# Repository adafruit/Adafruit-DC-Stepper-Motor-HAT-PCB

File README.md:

## Adafruit DC Stepper Motor HAT and Bonnet PCB
<a href="http://www.adafruit.com/products/2348"><br/>
Click here to purchase one from the Adafruit shop</a>

Let your robotic dreams come true with the new DC+Stepper Motor HAT from Adafruit. This Raspberry Pi add-on is perfect for any motion project as it can drive up to 4 DC or 2 Stepper motors with full PWM speed control.

Raspberry Pi and motors are not included. Works with any and all Raspberry Pi computers with 2x20 connection port.

Since the Raspberry Pi does not have a lot of PWM pins, we use a fully-dedicated PWM driver chip onboard to both control motor direction and speed. This chip handles all the motor and speed controls over I2C. Only two pins (SDA & SCL) are required to drive the multiple motors, and since it's I2C you can also connect any other I2C devices or HATs to the same pins.

In fact, you can even stack multiple Motor HATs, up to 32 of them, for controlling up to 64 stepper motors or 128 DC motors (or a mix of the two) - just remember to purchase and solder in a stacking header instead of the one we include.

Motors are controlled by TB6612 MOSFET drivers with 1.2A per channel current capability (you can draw up to 3A peak for approx 20ms at a time), a big improvement over L293D drivers and there are built-in flyback diodes as well.

PCB files for the Adafruit DC Stepper Motor Hat and Bonnet. The format is EagleCAD schematic and board layout
- https://www.adafruit.com/products/2348
- https://www.adafruit.com/product/4280

### License

Adafruit invests time and resources providing this open source design, please support Adafruit and open-source hardware by purchasing products from [Adafruit](https://www.adafruit.com)!

All text above must be included in any redistribution

Designed by Limor Fried/Ladyada for Adafruit Industries.
Creative Commons Attribution/Share-Alike, all text above must be included in any redistribution. 
See license.txt for additional information.

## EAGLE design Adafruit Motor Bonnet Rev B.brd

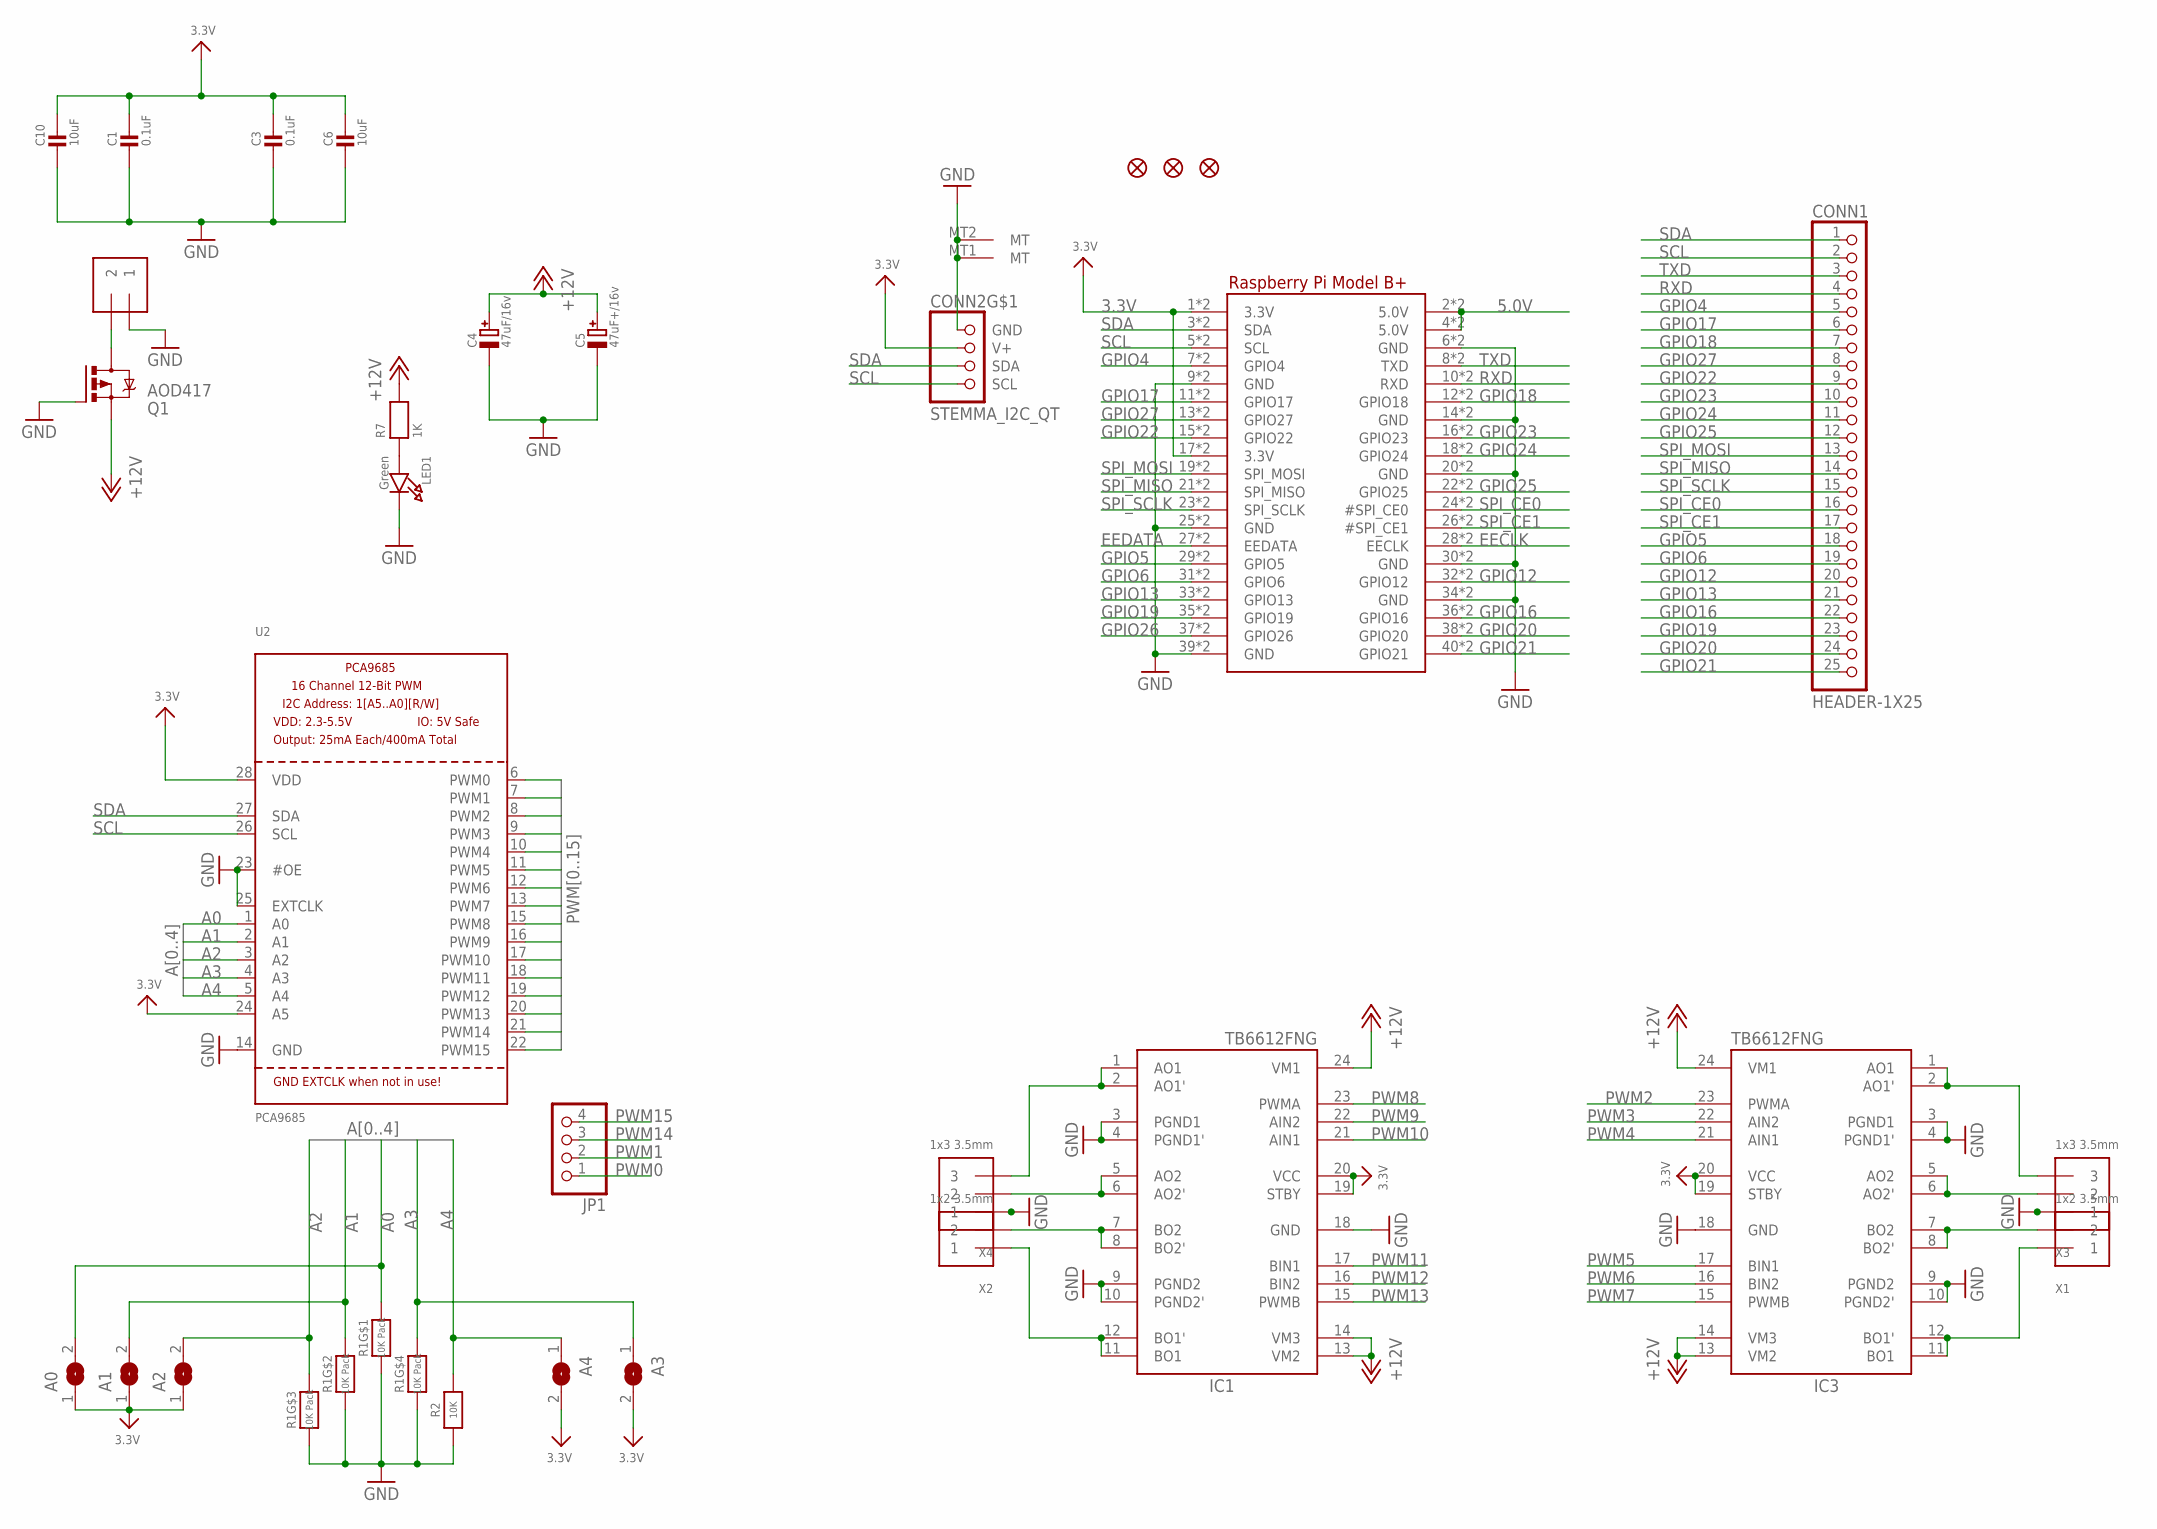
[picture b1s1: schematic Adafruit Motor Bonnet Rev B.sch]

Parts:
A0, A1, A2, A3, A4: SOLDERJUMPERREFLOW_NOPASTE; SOLDERJUMPER_REFLOW_NOPASTE
C1, C3: 0.1uF; 0603-NO
C4: 47uF/16v; PANASONIC_C
C5: 47uF+/16v; PANASONIC_C
C6, C10: 10uF; 0805-NO
CONN1: HEADER-1X25; 1X25_ROUND_70MIL
CONN2: STEMMA_I2C_QT; JST_SH4
FID1, FID2, FID3: FIDUCIAL_1MM
IC1, IC3: TB6612FNG; SSOP24
JP1: HEADER-1X4ROUND; 1X04_ROUND
LED1: Green; CHIPLED_0805_NOOUTLINE
MPOWER: 1x2 3.5mm; TERMBLOCK_1X2-3.5MM
Q1: AOD417; D-PAK_TO252AA
R1: 10K Pack; RESPACK_4X0603
R2: 10K; 0603-NO
R7: 1K; 0603-NO
RPI1: RASPBERRYPI_BPLUS_BONNET_THMSMT; PI_BONNET_THMSMT
U2: PCA9685; TSSOP28
X1, X2: 1x2 3.5mm; TERMBLOCK_1X2-3.5MM
X3, X4: 1x3 3.5mm; TERMBLOCK_1X3-3.5MM

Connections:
3.3V: A0.1, A1.1, A2.1, A3.2, A4.2, C1.1, C3.1, C6.1, C10.1, CONN2.2 (V+), IC1.19 (STBY), IC1.20 (VCC), IC3.19 (STBY), IC3.20 (VCC), RPI1.1 (3.3V), RPI1.17 (3.3V), RPI1.S1 (3.3V), RPI1.S17 (3.3V), U2.24 (A5), U2.28 (VDD)
5.0V: RPI1.2 (5.0V), RPI1.4 (5.0V), RPI1.S2 (5.0V), RPI1.S4 (5.0V)
+12V: C4.+, C5.+, IC1.13 (VM2), IC1.14 (VM3), IC1.24 (VM1), IC3.13 (VM2), IC3.14 (VM3), IC3.24 (VM1), Q1.3 (S), R7.2
A0: A0.2, R1.8 (2), U2.1 (A0)
A1: A1.2, R1.7 (2), U2.2 (A1)
A2: A2.2, R1.6 (2), U2.3 (A2)
A3: A3.1, R1.5 (2), U2.4 (A3)
A4: A4.1, R2.2, U2.5 (A4)
EECLK: RPI1.28 (EECLK), RPI1.S28 (EECLK)
EEDATA: RPI1.27 (EEDATA), RPI1.S27 (EEDATA)
GND: C1.2, C3.2, C4.-, C5.-, C6.2, C10.2, CONN2.1 (GND), CONN2.MT1 (MT), CONN2.MT2 (MT), IC1.3 (PGND1), IC1.4 (PGND1'), IC1.9 (PGND2), IC1.10 (PGND2'), IC1.18 (GND), IC3.3 (PGND1), IC3.4 (PGND1'), IC3.9 (PGND2), IC3.10 (PGND2'), IC3.18 (GND), LED1.C, MPOWER.1, Q1.1 (G), R1.1, R1.2 (1), R1.3 (1), R1.4 (1), R2.1, RPI1.6 (GND), RPI1.9 (GND), RPI1.14 (GND), RPI1.20 (GND), RPI1.25 (GND), RPI1.30 (GND), RPI1.34 (GND), RPI1.39 (GND), RPI1.S6 (GND), RPI1.S9 (GND), RPI1.S14 (GND), RPI1.S20 (GND), RPI1.S25 (GND), RPI1.S30 (GND), RPI1.S34 (GND), RPI1.S39 (GND), U2.14 (GND), U2.23 (#OE), U2.25 (EXTCLK), X3.1, X4.1
GPIO4: CONN1.5, RPI1.7 (GPIO4), RPI1.S7 (GPIO4)
GPIO5: CONN1.18, RPI1.29 (GPIO5), RPI1.S29 (GPIO5)
GPIO6: CONN1.19, RPI1.31 (GPIO6), RPI1.S31 (GPIO6)
GPIO12: CONN1.20, RPI1.32 (GPIO12), RPI1.S32 (GPIO12)
GPIO13: CONN1.21, RPI1.33 (GPIO13), RPI1.S33 (GPIO13)
GPIO16: CONN1.22, RPI1.36 (GPIO16), RPI1.S36 (GPIO16)
GPIO17: CONN1.6, RPI1.11 (GPIO17), RPI1.S11 (GPIO17)
GPIO18: CONN1.7, RPI1.12 (GPIO18), RPI1.S12 (GPIO18)
GPIO19: CONN1.23, RPI1.35 (GPIO19), RPI1.S35 (GPIO19)
GPIO20: CONN1.24, RPI1.38 (GPIO20), RPI1.S38 (GPIO20)
GPIO21: CONN1.25, RPI1.40 (GPIO21), RPI1.S40 (GPIO21)
GPIO22: CONN1.9, RPI1.15 (GPIO22), RPI1.S15 (GPIO22)
GPIO23: CONN1.10, RPI1.16 (GPIO23), RPI1.S16 (GPIO23)
GPIO24: CONN1.11, RPI1.18 (GPIO24), RPI1.S18 (GPIO24)
GPIO25: CONN1.12, RPI1.22 (GPIO25), RPI1.S22 (GPIO25)
GPIO26: RPI1.37 (GPIO26), RPI1.S37 (GPIO26)
GPIO27: CONN1.8, RPI1.13 (GPIO27), RPI1.S13 (GPIO27)
M1A: IC1.1 (AO1), IC1.2 (AO1'), X4.3
M1B: IC1.5 (AO2), IC1.6 (AO2'), X4.2
M2A: IC1.11 (BO1), IC1.12 (BO1'), X2.1
M2B: IC1.7 (BO2), IC1.8 (BO2'), X2.2
M3A: IC3.1 (AO1), IC3.2 (AO1'), X3.3
M3B: IC3.5 (AO2), IC3.6 (AO2'), X3.2
M4A: IC3.11 (BO1), IC3.12 (BO1'), X1.1
M4B: IC3.7 (BO2), IC3.8 (BO2'), X1.2
unnamed: LED1.A, R7.1
PWM0: JP1.1, U2.6 (PWM0)
PWM1: JP1.2, U2.7 (PWM1)
PWM2: IC3.23 (PWMA), U2.8 (PWM2)
PWM3: IC3.22 (AIN2), U2.9 (PWM3)
PWM4: IC3.21 (AIN1), U2.10 (PWM4)
PWM5: IC3.17 (BIN1), U2.11 (PWM5)
PWM6: IC3.16 (BIN2), U2.12 (PWM6)
PWM7: IC3.15 (PWMB), U2.13 (PWM7)
PWM8: IC1.23 (PWMA), U2.15 (PWM8)
PWM9: IC1.22 (AIN2), U2.16 (PWM9)
PWM10: IC1.21 (AIN1), U2.17 (PWM10)
PWM11: IC1.17 (BIN1), U2.18 (PWM11)
PWM12: IC1.16 (BIN2), U2.19 (PWM12)
PWM13: IC1.15 (PWMB), U2.20 (PWM13)
PWM14: JP1.3, U2.21 (PWM14)
PWM15: JP1.4, U2.22 (PWM15)
RXD: CONN1.4, RPI1.10 (RXD), RPI1.S10 (RXD)
SCL: CONN1.2, CONN2.4 (SCL), RPI1.5 (SCL), RPI1.S5 (SCL), U2.26 (SCL)
SDA: CONN1.1, CONN2.3 (SDA), RPI1.3 (SDA), RPI1.S3 (SDA), U2.27 (SDA)
SPI_CE0: CONN1.16, RPI1.24 (#SPI_CE0), RPI1.S24 (#SPI_CE0)
SPI_CE1: CONN1.17, RPI1.26 (#SPI_CE1), RPI1.S26 (#SPI_CE1)
SPI_MISO: CONN1.14, RPI1.21 (SPI_MISO), RPI1.S21 (SPI_MISO)
SPI_MOSI: CONN1.13, RPI1.19 (SPI_MOSI), RPI1.S19 (SPI_MOSI)
SPI_SCLK: CONN1.15, RPI1.23 (SPI_SCLK), RPI1.S23 (SPI_SCLK)
TXD: CONN1.3, RPI1.8 (TXD), RPI1.S8 (TXD)
VMOTOR: MPOWER.2, Q1.4 (D)

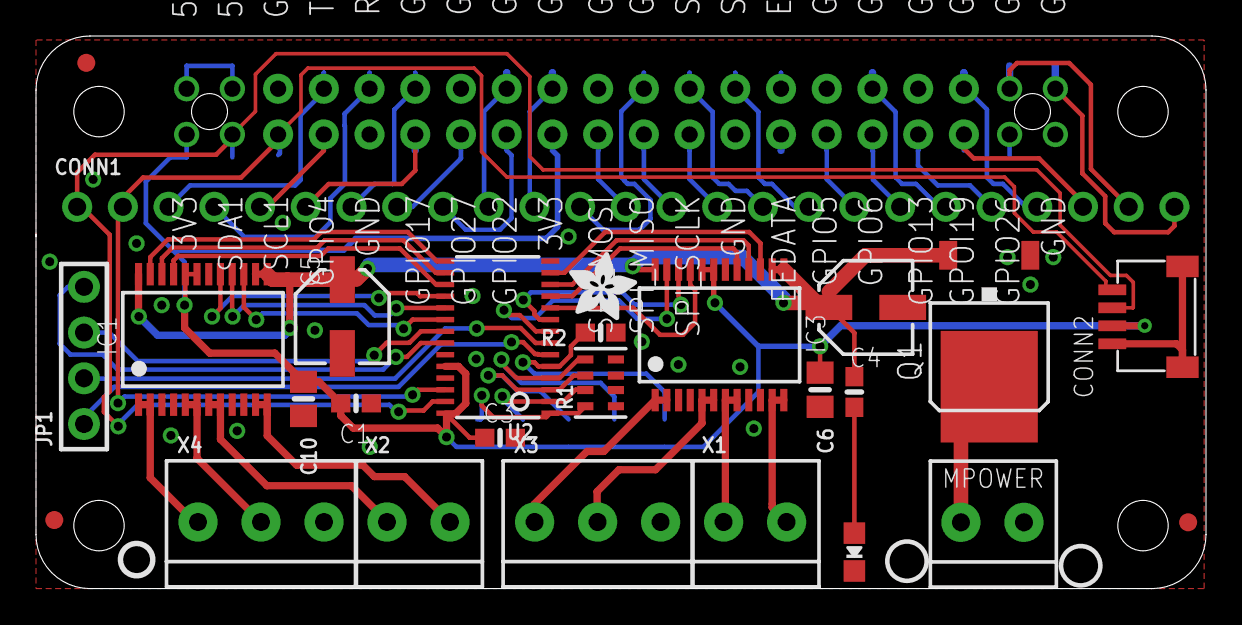
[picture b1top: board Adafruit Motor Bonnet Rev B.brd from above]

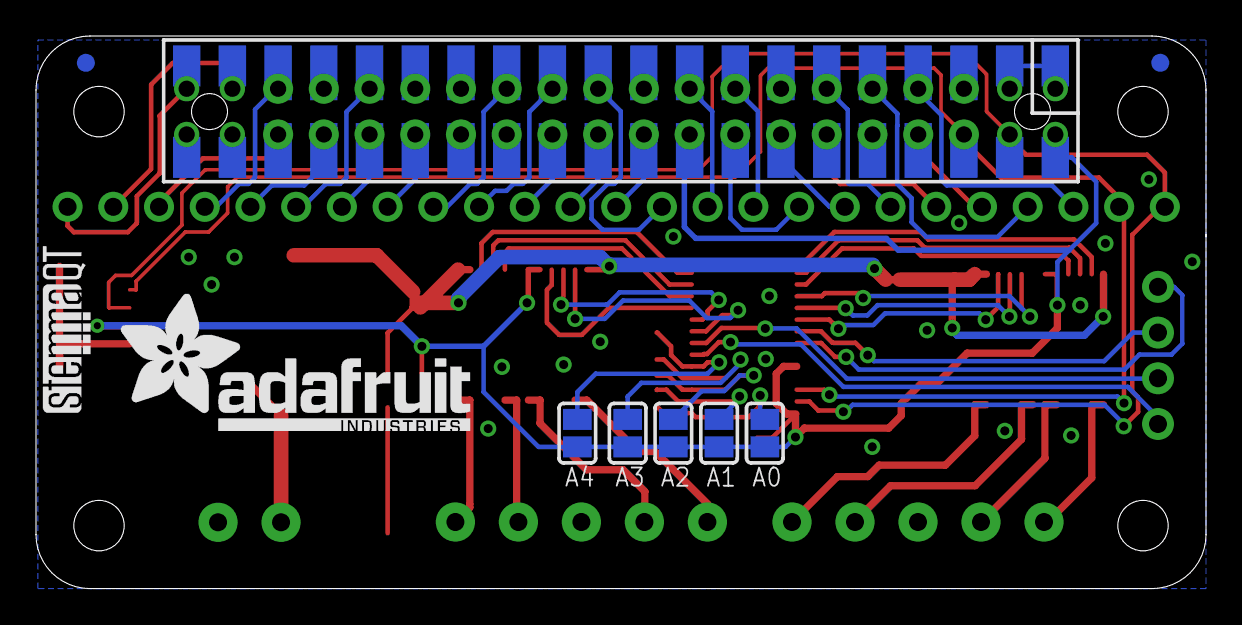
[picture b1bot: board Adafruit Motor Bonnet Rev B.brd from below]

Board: 2 copper layers, 65.0 x 30.7 mm, 82 parts (13 on the bottom side), 63 nets.

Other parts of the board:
PLABEL0: PLABEL0
PLABEL1: PLABEL1
PLABEL2: PLABEL2
PLABEL3: PLABEL3
PLABEL4: PLABEL4
PLABEL5: PLABEL5
PLABEL6: PLABEL6
PLABEL7: PLABEL7
PLABEL8: PLABEL8
PLABEL9: PLABEL9
PLABEL10: PLABEL10
PLABEL11: PLABEL11
PLABEL12: PLABEL12
PLABEL13: PLABEL13
PLABEL14: PLABEL14
PLABEL15: PLABEL15
PLABEL16: PLABEL16
PLABEL17: PLABEL17
PLABEL18: PLABEL18
PLABEL19: PLABEL19
PLABEL20: PLABEL20
PLABEL21: PLABEL21
PLABEL22: PLABEL22
PLABEL23: PLABEL23
PLABEL24: PLABEL24
PLABEL25: PLABEL25
PLABEL26: PLABEL26
PLABEL27: PLABEL27
PLABEL28: PLABEL28
PLABEL29: PLABEL29
PLABEL30: PLABEL30
PLABEL31: PLABEL31
PLABEL33: PLABEL33
PLABEL34: PLABEL34
PLABEL35: PLABEL35
PLABEL36: PLABEL36
PLABEL37: PLABEL37
PLABEL38: PLABEL38
PLABEL39: PLABEL39
PLABEL40: PLABEL40
PLABEL41: PLABEL41
PLABEL42: PLABEL42
PLABEL43: PLABEL43
PLABEL44: PLABEL44
PLABEL45: PLABEL45
PLABEL46: PLABEL46
PLABEL47: PLABEL47
U$6: PCBFEAT-REV-040
U$8: ADAFRUIT_TEXT_20MM
U$14: ADAFRUIT_3.5MM
U$15: STEMMAQT

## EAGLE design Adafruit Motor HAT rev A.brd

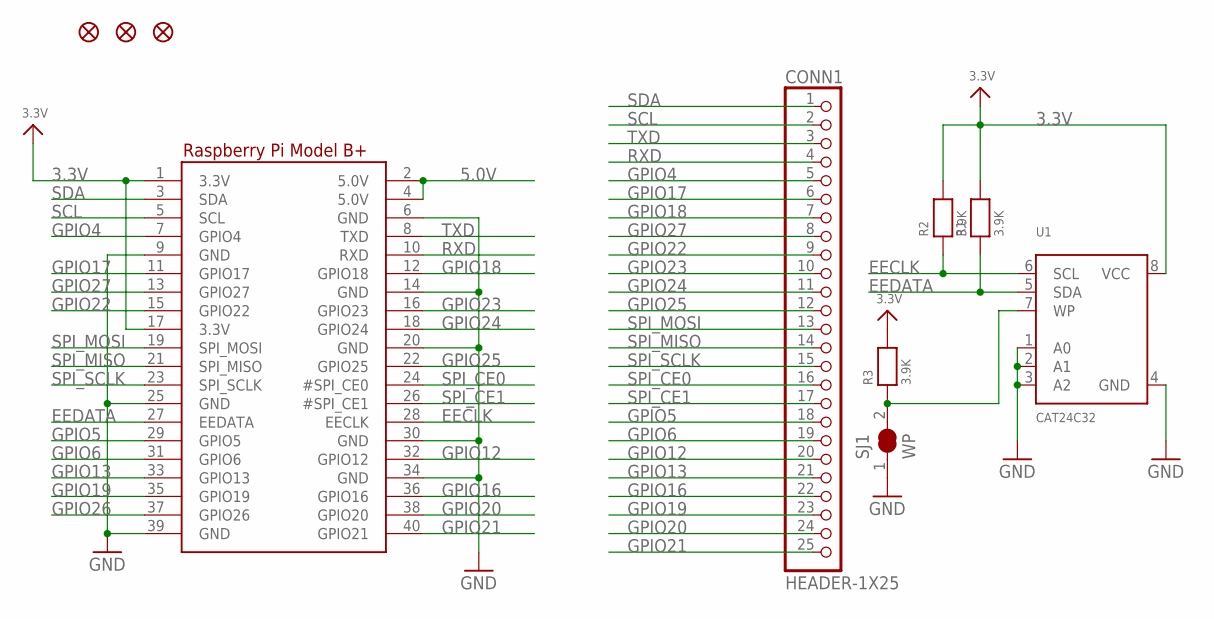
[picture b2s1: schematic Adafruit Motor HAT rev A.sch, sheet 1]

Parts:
CONN1: HEADER-1X25; 1X25_ROUND_70MIL
FID1, FID2, FID3: FIDUCIAL""; FIDUCIAL_1MM
R1, R2, R3: 3.9K; 0805-NO
RPI1: RASPBERRYPI_BPLUS_HATSLOTS; PI_HAT_SLOTS
SJ1: WP; SOLDERJUMPER_CLOSEDWIRE
U1: CAT24C32; SOIC8_150MIL

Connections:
3.3V: R1.2, R2.2, R3.2, RPI1.1 (3.3V), RPI1.17 (3.3V), U1.8 (VCC); also elsewhere on the board
5.0V: RPI1.2 (5.0V), RPI1.4 (5.0V)
EECLK: R2.1, RPI1.28 (EECLK), U1.6 (SCL)
EEDATA: R1.1, RPI1.27 (EEDATA), U1.5 (SDA)
GND: RPI1.6 (GND), RPI1.9 (GND), RPI1.14 (GND), RPI1.20 (GND), RPI1.25 (GND), RPI1.30 (GND), RPI1.34 (GND), RPI1.39 (GND), SJ1.1, U1.1 (A0), U1.2 (A1), U1.3 (A2), U1.4 (GND); also elsewhere on the board
GPIO4: CONN1.5, RPI1.7 (GPIO4)
GPIO5: CONN1.18, RPI1.29 (GPIO5)
GPIO6: CONN1.19, RPI1.31 (GPIO6)
GPIO12: CONN1.20, RPI1.32 (GPIO12)
GPIO13: CONN1.21, RPI1.33 (GPIO13)
GPIO16: CONN1.22, RPI1.36 (GPIO16)
GPIO17: CONN1.6, RPI1.11 (GPIO17)
GPIO18: CONN1.7, RPI1.12 (GPIO18)
GPIO19: CONN1.23, RPI1.35 (GPIO19)
GPIO20: CONN1.24, RPI1.38 (GPIO20)
GPIO21: CONN1.25, RPI1.40 (GPIO21)
GPIO22: CONN1.9, RPI1.15 (GPIO22)
GPIO23: CONN1.10, RPI1.16 (GPIO23)
GPIO24: CONN1.11, RPI1.18 (GPIO24)
GPIO25: CONN1.12, RPI1.22 (GPIO25)
GPIO26: RPI1.37 (GPIO26)
GPIO27: CONN1.8, RPI1.13 (GPIO27)
unnamed: R3.1, SJ1.2, U1.7 (WP)
RXD: CONN1.4, RPI1.10 (RXD)
SCL: CONN1.2, RPI1.5 (SCL); also elsewhere on the board
SDA: CONN1.1, RPI1.3 (SDA); also elsewhere on the board
SPI_CE0: CONN1.16, RPI1.24 (#SPI_CE0)
SPI_CE1: CONN1.17, RPI1.26 (#SPI_CE1)
SPI_MISO: CONN1.14, RPI1.21 (SPI_MISO)
SPI_MOSI: CONN1.13, RPI1.19 (SPI_MOSI)
SPI_SCLK: CONN1.15, RPI1.23 (SPI_SCLK)
TXD: CONN1.3, RPI1.8 (TXD)

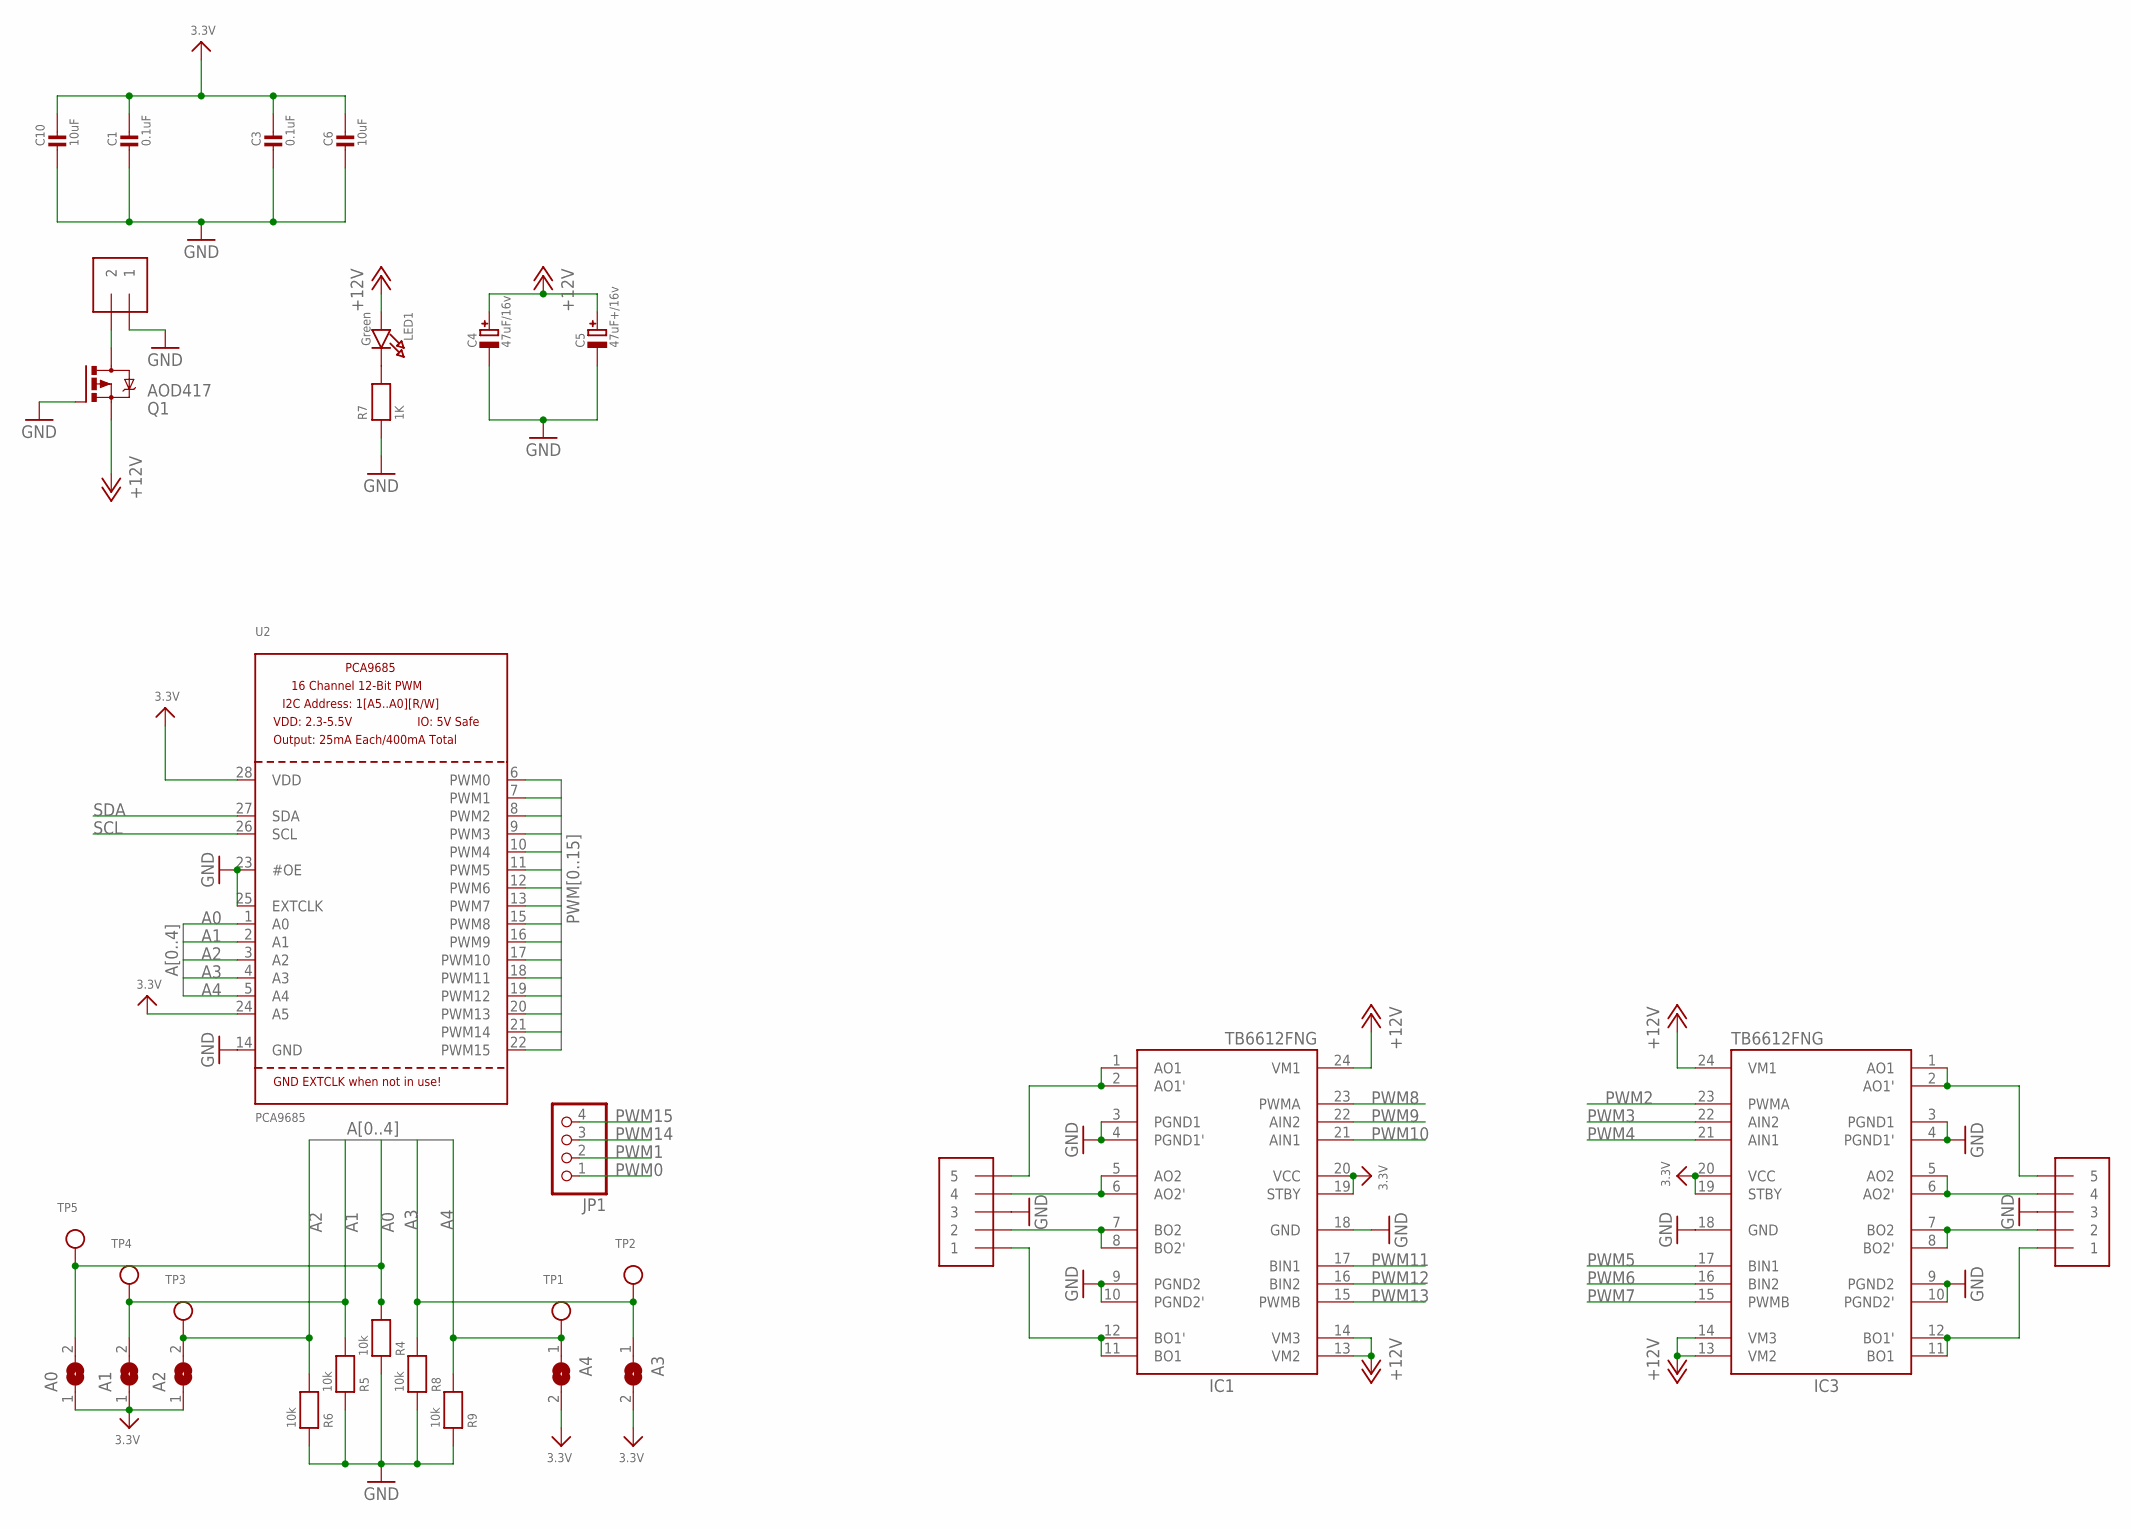
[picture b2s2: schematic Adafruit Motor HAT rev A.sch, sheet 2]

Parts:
A0, A1, A2, A3, A4: SOLDERJUMPERREFLOW_NOPASTE; SOLDERJUMPER_REFLOW_NOPASTE
C1, C3: 0.1uF; 0805-NO
C4: 47uF/16v; PANASONIC_C
C5: 47uF+/16v; PANASONIC_C
C6, C10: 10uF; 0805-NO
IC1, IC3: TB6612FNG; SSOP24
J1, J3: 1X5; 1X05-3.5MM
JP1: HEADER-1X476MIL; 1X04_ROUND_76
LED1: Green; CHIPLED_0805_NOOUTLINE
MPOWER: 1X2-3.5MM
Q1: AOD417; D-PAK_TO252AA
R4, R5, R6, R8, R9: 10k; 0805-NO
R7: 1K; 0805-NO
TP1, TP2, TP3, TP4, TP5: TESTPOINTROUND2MM; TESTPOINT_ROUND_2MM
U2: PCA9685; TSSOP28

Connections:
3.3V: A0.1, A1.1, A2.1, A3.2, A4.2, C1.1, C3.1, C6.1, C10.1, IC1.19 (STBY), IC1.20 (VCC), IC3.19 (STBY), IC3.20 (VCC), U2.24 (A5), U2.28 (VDD); also elsewhere on the board
+12V: C4.+, C5.+, IC1.13 (VM2), IC1.14 (VM3), IC1.24 (VM1), IC3.13 (VM2), IC3.14 (VM3), IC3.24 (VM1), LED1.A, Q1.3 (S)
A0: A0.2, R4.2, TP5.P$1, U2.1 (A0)
A1: A1.2, R5.2, TP4.P$1, U2.2 (A1)
A2: A2.2, R6.2, TP3.P$1, U2.3 (A2)
A3: A3.1, R8.2, TP2.P$1, U2.4 (A3)
A4: A4.1, R9.2, TP1.P$1, U2.5 (A4)
GND: C1.2, C3.2, C4.-, C5.-, C6.2, C10.2, IC1.3 (PGND1), IC1.4 (PGND1'), IC1.9 (PGND2), IC1.10 (PGND2'), IC1.18 (GND), IC3.3 (PGND1), IC3.4 (PGND1'), IC3.9 (PGND2), IC3.10 (PGND2'), IC3.18 (GND), J1.3, J3.3, MPOWER.1, Q1.1 (G), R4.1, R5.1, R6.1, R7.1, R8.1, R9.1, U2.14 (GND), U2.23 (#OE), U2.25 (EXTCLK); also elsewhere on the board
unnamed: MPOWER.2, Q1.4 (D)
unnamed: IC1.1 (AO1), IC1.2 (AO1'), J1.5
unnamed: IC1.5 (AO2), IC1.6 (AO2'), J1.4
unnamed: IC1.7 (BO2), IC1.8 (BO2'), J1.2
unnamed: IC1.11 (BO1), IC1.12 (BO1'), J1.1
unnamed: IC3.1 (AO1), IC3.2 (AO1'), J3.5
unnamed: IC3.5 (AO2), IC3.6 (AO2'), J3.4
unnamed: IC3.7 (BO2), IC3.8 (BO2'), J3.2
unnamed: IC3.11 (BO1), IC3.12 (BO1'), J3.1
unnamed: LED1.C, R7.2
PWM0: JP1.1, U2.6 (PWM0)
PWM1: JP1.2, U2.7 (PWM1)
PWM2: IC3.23 (PWMA), U2.8 (PWM2)
PWM3: IC3.22 (AIN2), U2.9 (PWM3)
PWM4: IC3.21 (AIN1), U2.10 (PWM4)
PWM5: IC3.17 (BIN1), U2.11 (PWM5)
PWM6: IC3.16 (BIN2), U2.12 (PWM6)
PWM7: IC3.15 (PWMB), U2.13 (PWM7)
PWM8: IC1.23 (PWMA), U2.15 (PWM8)
PWM9: IC1.22 (AIN2), U2.16 (PWM9)
PWM10: IC1.21 (AIN1), U2.17 (PWM10)
PWM11: IC1.17 (BIN1), U2.18 (PWM11)
PWM12: IC1.16 (BIN2), U2.19 (PWM12)
PWM13: IC1.15 (PWMB), U2.20 (PWM13)
PWM14: JP1.3, U2.21 (PWM14)
PWM15: JP1.4, U2.22 (PWM15)
SCL: U2.26 (SCL); also elsewhere on the board
SDA: U2.27 (SDA); also elsewhere on the board

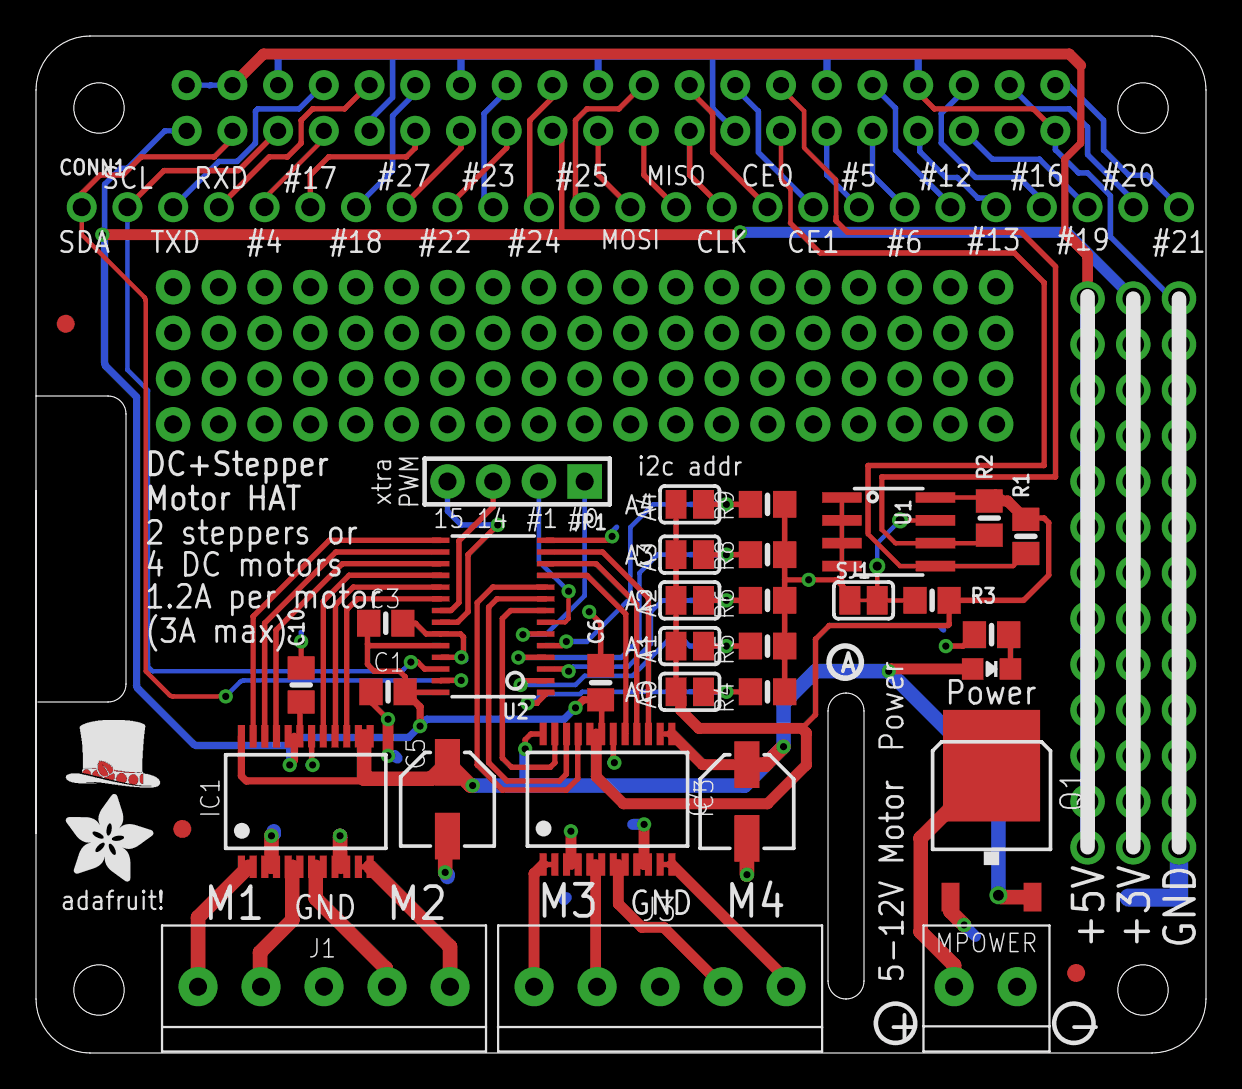
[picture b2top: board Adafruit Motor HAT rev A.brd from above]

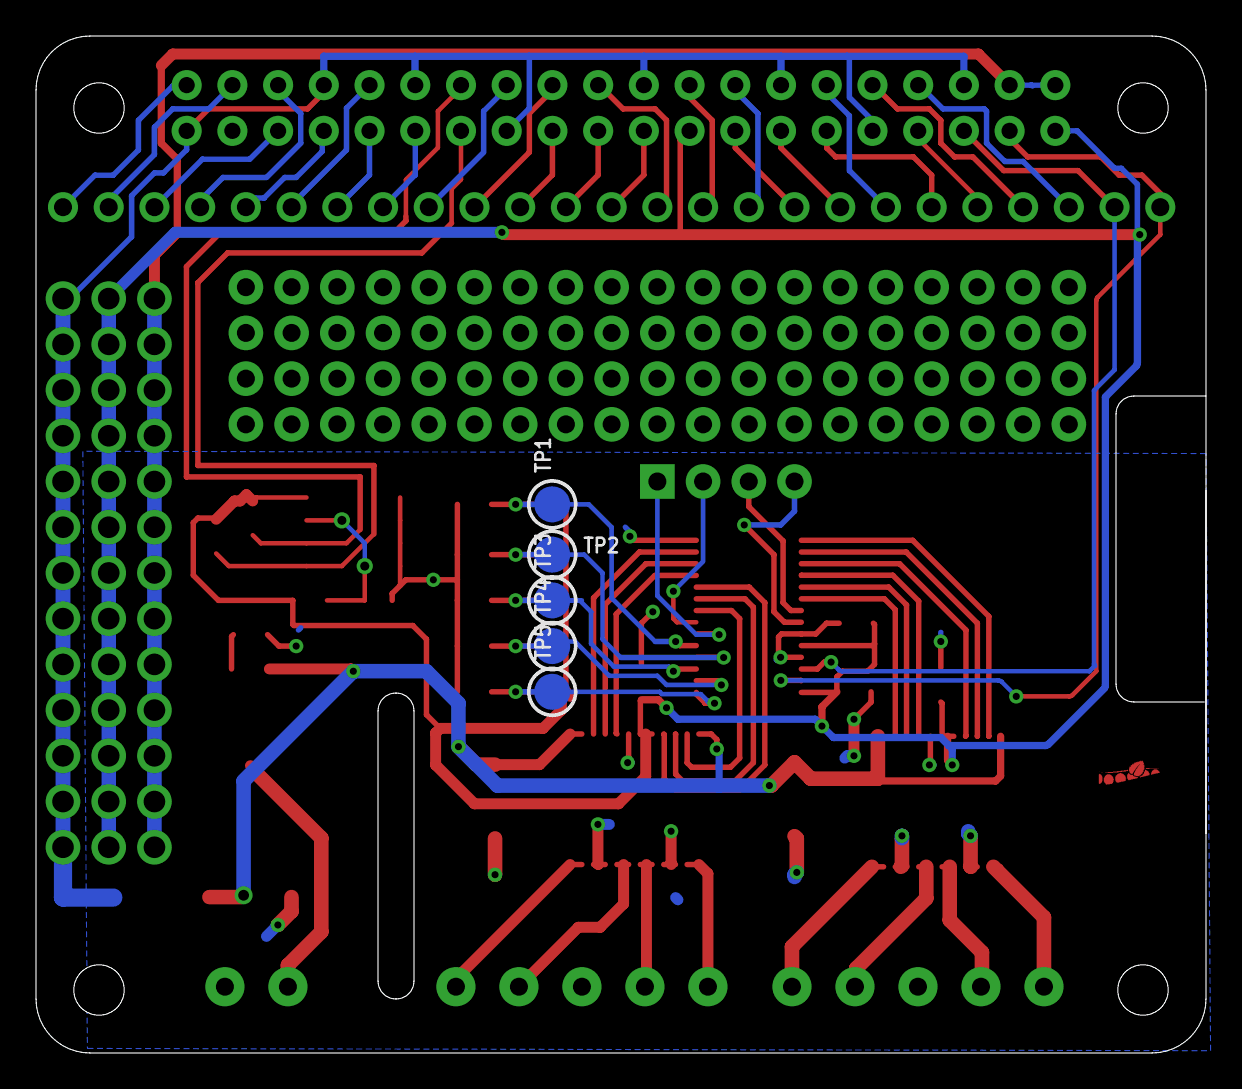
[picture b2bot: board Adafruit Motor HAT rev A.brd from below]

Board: 2 copper layers, 65.0 x 56.5 mm, 44 parts (5 on the bottom side), 63 nets.

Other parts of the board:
U$5: PIHATLOGO
U$6: PCBFEAT-REV-040
U$51: ADAFRUIT_5MM

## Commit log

2016-05-19 files!
2022-06-17 Added Motor Bonnet files
2026-04-14 add bonnet rev b

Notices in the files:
parts and their libraries:
microbuilder: This work is placed in the public domain, and may be freely used for commercial and non-commercial work with the following conditions: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
